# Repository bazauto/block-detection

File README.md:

# 2-Channel DCC Block Detector (Active High)

CT-based occupancy detection for the Westgate Hollow layout. Two independent
channels, each turning the current in an external current transformer into a
push-pull logic level: **HIGH (3.3 V) = block occupied, LOW (0 V) = clear**.

Single +3.3 V rail, fed in through the output header. Board is **48 × 38 mm**,
2 layers, four M2 mounting holes.

## Why build this

**So that a broken cable or connection under the layout doesn't register as a
clear block.**

The off-the-shelf detectors used so far are active low: they pull their output to
0 V when a block is occupied, and leave it open when clear. The feedback node's
inputs are pulled up, so a broken wire floats high, and that reads exactly like a
clear block, the permissive state (`bazauto/layout-feedback#9`).

This board is **active high**: occupied drives 3.3 V, clear drives 0 V. A broken
wire into a pulled-up input now floats to the *occupied* side.

## Status

**Revision 1.0: 10 boards ordered from PCBWay, awaiting delivery.** Nothing has
been measured on hardware yet.

---

## Files

| File | What it is |
|---|---|
| `bazauto-block-detection.kicad_sch` | Schematic (KiCad 10 format) |
| `bazauto-block-detection.kicad_pcb` | 2-layer PCB, fully routed |
| `bazauto-block-detection.kicad_sym` | Project symbols: `TLV9002IDGKR`, `TLV3212IDGKR` |
| `sym-lib-table` | Project symbol library table. There is no project footprint table: every footprint comes from the stock KiCad libraries and is stored in the board file |
| `bom.csv` | Bill of materials, grouped |
| `fab/rev-1.0/` | **Revision 1.0 as sent to fab**: Gerbers, drill files, Gerber job file, position file, the zipped Gerber set, and `SOURCE.txt` fingerprinting the board they came from. See [Fabrication revisions](#fabrication-revisions) |
| `BOM_PCBWay_bazauto-block-detection.xlsx` | **Not in the repo.** `bom.csv` poured into PCBWay's template, ready to upload. Generate it locally; see [Regenerating](#regenerating) |
| `scripts/` | Generators and checkers — see [Regenerating](#regenerating) |

Everything else (resistors, caps, diodes, connectors, trimmers) comes from the
stock KiCad 10 libraries, so the project opens on any standard install.

---

## Circuit

Each channel is the same chain:

```
CT ─ terminal block ─ burden ─ ESD clamp ─ 1k ─ precision peak detector ─ comparator ─ OUT
     J1 / J2          R1,R2,R3  D1 / D2   R4/R5   U1 + D3/D4 + C3/C4 + R8/R9   U2      J3
                      + JP1
```

**Burden.** The CT secondary is loaded across the input terminals.
Channel 1 is switchable, channel 2 is fixed:

| Channel | JP1 | Burden | Use |
|---|---|---|---|
| 1 | open | 1.1 kΩ | Programming track (service-mode ACK pulse) |
| 1 | fitted | 1.1 k ∥ 110 R = **100.0 Ω** | Standard track |
| 2 | — | 100 Ω fixed | Standard track only |

The parallel combination is exact: 1100 × 110 / 1210 = 100.0 Ω.

**Clamp.** D1/D2 (BAT54S, series pair) clamp the input to roughly −0.3 V /
+3.6 V. R4/R5 (1 k) then limit the current into the op-amp's input structure on
the negative half-cycle — the CT output is bipolar and a single-supply op-amp
input sits at the very edge of its absolute maximum without them.

**Peak detector.** The op-amp drives D3/D4 with the diode *inside* the feedback
loop, so the forward drop is divided out by the loop gain — no 0.6 V loss on a
signal this small. R6/R7 (100 Ω) sit between the op-amp output and the diode:
they are inside the loop too, and stop the RRIO output from ringing into the
10 µF hold capacitor. C3/C4 hold the envelope, R8/R9 bleed it away.

**Comparator.** The envelope goes to +IN, the trimmer wiper to −IN, and the
push-pull output drives the header directly. R10/R11 (10 M) add positive
feedback so the output does not chatter as the envelope crosses the threshold.

---

## Setting up

Time constants and tuning, all measurable on the board:

- **Release time.** R8/R9 × C3/C4 = 100 kΩ × 10 µF ≈ **1 s** to decay. That
  doubles as debounce for dirty wheels. For a faster release drop the bleed
  resistor — 10 k gives ≈ 100 ms.
- **Hysteresis.** V_hyst ≈ 3.3 V × R_bleed / R_hyst = 3.3 × 100 k / 10 M
  ≈ **33 mV**. Lower R10/R11 for more.
- **Threshold.** With the block clear, turn RVn until OUTn just goes low, then
  back off about 10 %.

Test points, all on the top side:

| TP | Net | Use |
|---|---|---|
| TP1 / TP3 | VREF1 / VREF2 | Trimmer wiper — the threshold you have dialled in |
| TP2 / TP4 | ENV1 / ENV2 | Peak-detector output — the rectified envelope |
| TP5 | GND | Scope ground |

---

## ⚠ Known concerns with revision 1.0

**1. The signal chain has no gain, and that makes the threshold hard to set.**

This is the one thing worth changing. The detector is a unity-gain rectifier, so
the comparator threshold has to be set in the millivolt region. With a 1:100 CT
and a 100 Ω burden, 10 mA of track current gives about 10 mV at the envelope
node. The trimmer spans the full 0–3.3 V across 10 kΩ, so 10 mV is **0.3 % of
its travel** — a fraction of one turn on a 12-turn trimmer — and it is the same
order as the comparator's own input offset voltage. Setting it repeatably will
be unpleasant, and it will drift.

The cheap fix is one resistor: put ~330 kΩ in series between +3V3 and the top of
each trimmer (RV1 pin 1, RV2 pin 1). The wiper then covers roughly 0–100 mV
instead of 0–3.3 V, giving about 30× the resolution and swamping nothing else.
The alternative is to give the op-amp stage gain instead of running it at unity.

**Revision 1.0, as ordered, does not include this change** (there is no 330 kΩ
part in `bom.csv`). Sizing it properly needs the CT's actual turns ratio. It
affects two nets and about 4 mm of track.

**2. Verify the TLV3212IDGKR pinout against the datasheet.** The comparator
symbol uses the industry-standard 8-pin dual layout — 1=OUTA, 2=INA−, 3=INA+,
4=GND, 5=INB+, 6=INB−, 7=OUTB, 8=V+ — which is what TLV3202IDGKR uses in the
same DGK package. I could not confirm TLV3212's pin assignment from a datasheet
in this session. **TLV3202IDGKR is a verified drop-in** if you would rather not
check. Same for TLV9002IDGKR, though that one follows the universal dual-op-amp
pinout and is not in doubt.

**3. AGND is the plane, not a separate net.** The spec asked for the filter
returns to go to AGND *and* for a solid, unbroken ground plane. Those pull in
opposite directions — a genuine second net needs a split, and a split is exactly
what section 6 forbids. I used one continuous GND pour and kept the analog
returns physically local instead: C3/C4 and R8/R9 ground through their own vias
straight into the plane, a few millimetres from the op-amp's own ground via.

---

## Layout

- **B.Cu is a ground pour.** F.Cu carries the signals plus a second GND pour in
  the gaps. 30 ground vias tie the two together: 16 taking SMD ground pads
  straight down to the plane, 14 stitching the pours across the board.
- **+3V3** runs as a perimeter ring (top edge, right edge, bottom edge) with a
  spine threaded through the gap between the two pad rows of U1 and U2, so it
  never crosses a channel's signal path.
- The two channels are mirrored top and bottom about the board centreline, with
  the shared dual op-amp and comparator between them. Both ICs are rotated so
  channel A faces the top band and channel B the bottom.
- 0.1 µF decoupling (C1, C2) sits against each IC's V+ pin; C5 is the 10 µF bulk.

**Where the ground plane is interrupted.** Four short bottom-layer hops let
crossing nets pass each other, 8.60 mm of track in total on a 1824 mm² board:

| Net | From → to | Length |
|---|---|---|
| +3V3 | (20.20, 22.00) → (20.20, 24.00) | 2.00 mm |
| /OUT1 | (42.20, 18.30) → (43.80, 18.30) | 1.60 mm |
| /OUT2 | (31.90, 22.60) → (33.45, 22.60) | 1.55 mm |
| OA2 out | (21.50, 22.75) → (21.50, 26.20) | 3.45 mm |

`scripts/check_plane.py` audits this and reports which analog nets pass over a
void. Current result: **the CT input rails, both op-amp inputs, ENV1 and VREF1
have completely unbroken copper beneath them.** Four crossings remain, all in
channel 2's middle band — ENV2 twice, VREF2 once, channel 2's op-amp output
once — and in each the trace crosses a void under 1 mm wide. Those nets carry a
rectified DC envelope and a DC threshold reference, where a sub-millimetre
detour in the return path at DCC frequencies is not a real effect. If you want them gone, the honest fix is a 4-layer stack-up, not
more clever 2-layer routing.

One placement change from your version: **C1 moved 0.65 mm right** (to x = 23.45)
so that channel 2's feedback trace and op-amp output each get their own corridor
past it. Everything else is where you left it.

---

## Regenerating

Run with KiCad's bundled Python, from the project directory:

```sh
K="C:/Program Files/KiCad/10.0"

python scripts/gen_schematic.py         # schematic + project symbol lib
python scripts/verify_netlist.py        # netlist vs. design intent
"$K/bin/python.exe" scripts/route_pcb.py    # routing + pours (placement is preserved)
"$K/bin/python.exe" scripts/check_board.py  # placement + board-vs-schematic nets
"$K/bin/python.exe" scripts/check_plane.py  # ground-plane audit
```

`route_pcb.py` loads the existing board, so hand-adjusted placement and
silkscreen survive; it only rebuilds tracks, vias and zones.

| Script | Does |
|---|---|
| `gen_schematic.py` | Builds the schematic from real KiCad library symbols; wires are computed from actual pin coordinates |
| `kicadlib.py` | S-expression reader/writer and symbol-library helpers |
| `probe_transform.py` | Derives KiCad's symbol placement transform empirically from its own demo files |
| `verify_netlist.py` | Compares the extracted netlist against the intended one, net by net |
| `route_pcb.py` | Routing, ground pours, silkscreen legends |
| `check_board.py` | Courtyard overlaps, off-board parts, board nets vs. schematic |
| `check_plane.py` | Bottom-layer voids and which analog nets cross them |
| `make_pcbway_bom.py` | Fills PCBWay's BOM template; fails if it has drifted from `bom.csv`. Needs PCBWay's sample BOM template saved locally as `Sample_BOM_PCBWay.xlsx`. It's PCBWay's file, so it isn't committed, and neither is the output. |
| `check_fab_outputs.py` | Checks the newest `fab/rev-X.Y/` against the board it was generated from; `--record` writes that revision's `SOURCE.txt`. Plain Python, needs `kicad-cli` on PATH or `KICAD_CLI` set |

---

## Fabrication revisions

Each set of files sent to a board house lives in its own `fab/rev-X.Y/` folder
and is never regenerated in place, so the repo always holds exactly what a
revision was. Each revision is also tagged in git (`rev-1.0`).

`fab/rev-X.Y/SOURCE.txt` records the SHA-256 of the board file (line endings
normalised) that its outputs came from. CI runs `scripts/check_fab_outputs.py`:

- **Board unchanged since the newest revision:** it regenerates the outputs and
  fails if the committed ones differ. That catches Gerbers left stale after a
  board edit, and a zip that disagrees with the loose files. Gerbers are compared
  by the geometry they draw, because KiCad doesn't write primitives in a stable
  order.
- **Board changed:** work on the next revision is under way. It reports a notice
  and passes.

To cut a new revision, for example 1.1:

1. Plot Gerbers, drill files (Excellon, PTH and NPTH separate) and the position
   file (CSV, mm, both sides) into `fab/rev-1.1/`, and zip the Gerbers, the
   Gerber job file and the drill files as `bazauto-block-detection.zip` there.
2. `python scripts/check_fab_outputs.py --record rev-1.1`
3. `python scripts/check_fab_outputs.py`, which must report all outputs matching.
4. Land it through a PR, then tag the merge commit `rev-1.1`.

---

## Verification

Everything below was run against the files in this directory:

```
kicad-cli sch erc            0 errors, 0 warnings
verify_netlist.py            all 17 nets match design intent, no unconnected pins
kicad-cli pcb drc            0 violations, 0 unconnected items
check_board.py               37 footprints, 0 problems (no overlaps, nets match schematic)
check_plane.py               8.60 mm bottom-layer track; 4 analog crossings (see above)
```

CI re-runs the two `kicad-cli` checks and `check_fab_outputs.py` on every pull
request (see `.github/workflows/ci.yml`). DRC there runs with `--schematic-parity` at error
severity. At warning severity the parity check reports 80 cosmetic mismatches:
footprints saved without their library prefix, and field text such as a
Datasheet of `''` against `~`. None is a net or connection mismatch.

Gerbers and drill files for revision 1.0 are in `fab/rev-1.0/`, and regenerating
them from the current board reproduces them exactly. Nothing has been measured on
hardware yet. The threshold-resolution concern above is analysis, not a bench
result.

---

## Licence

Copyright © 2026 Paul Barrett.

| Material | Licence |
|---|---|
| **The hardware design**: schematic, board, project symbol library, BOM, Gerbers and drill files, and the enclosure model (`enclosure/`, except `check_fit.py`) | [CERN-OHL-P-2.0](LICENSE) |
| **Software**: everything in `scripts/`, and `enclosure/check_fit.py` | [MIT](LICENSE-MIT) |

Source location: <https://github.com/bazauto/block-detection>

Third-party material, notably the KiCad library symbols the project symbols are
derived from, is listed in [THIRD-PARTY-NOTICES.md](THIRD-PARTY-NOTICES.md).

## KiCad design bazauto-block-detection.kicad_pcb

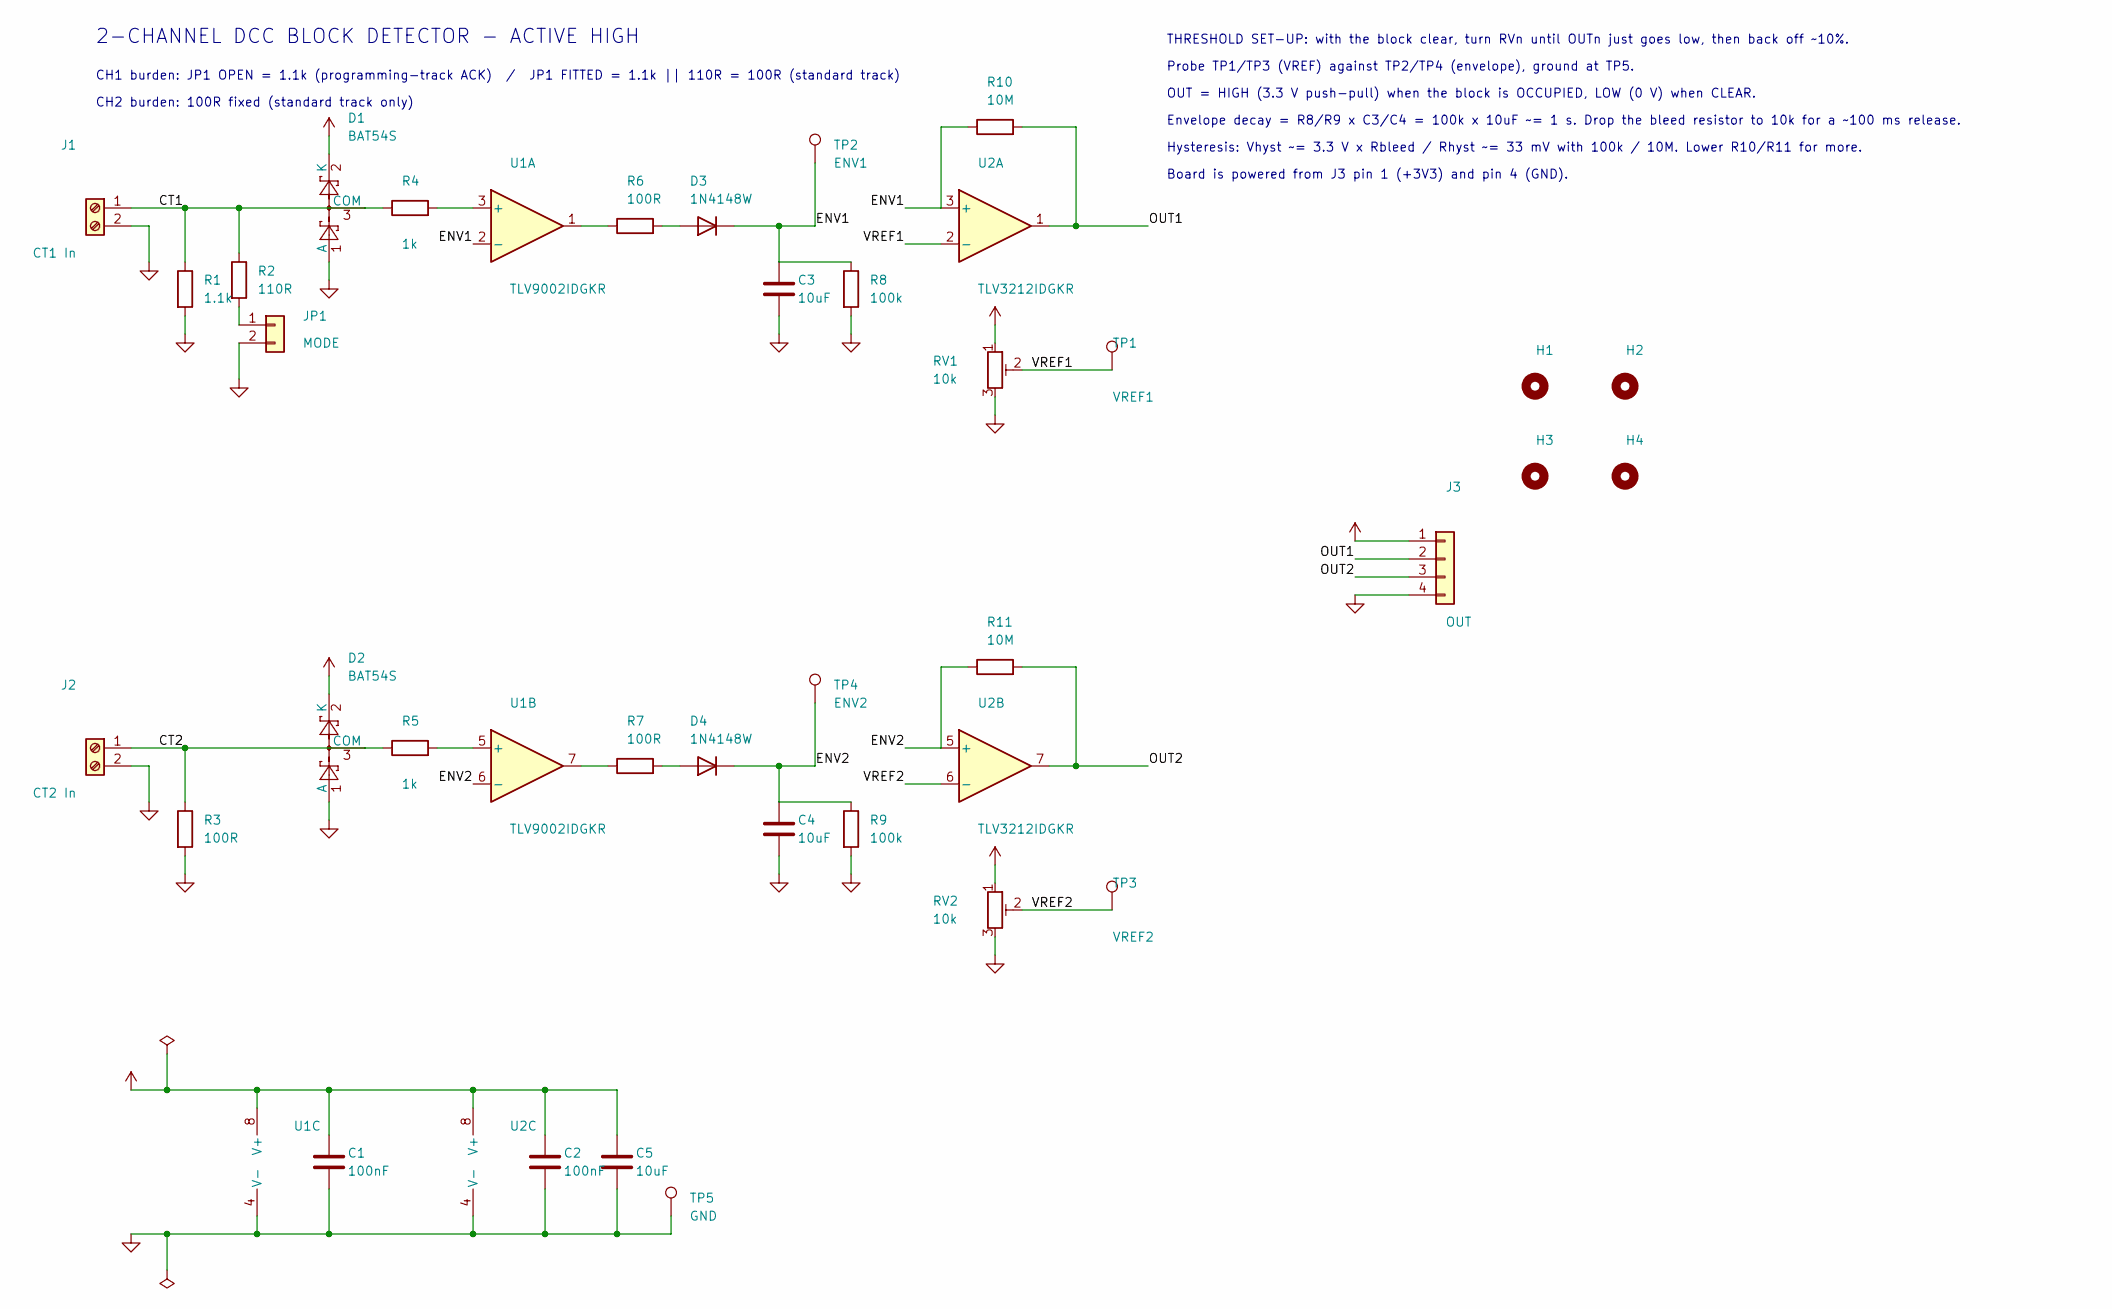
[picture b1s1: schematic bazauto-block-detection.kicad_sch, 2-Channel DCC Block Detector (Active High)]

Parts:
C1, C2: 100nF; C_0805_2012Metric; Voltage 25V
C3, C4, C5: 10uF; C_0805_2012Metric; Voltage 25V
D1, D2: BAT54S; SOT-23
D3, D4: 1N4148W; D_SOD-123
H1, H2, H3, H4: MountingHole; MountingHole_2.2mm_M2
J1: CT1 In; TerminalBlock_Phoenix_PT-1,5-2-3.5-H_1x02_P3.50mm_Horizontal
J2: CT2 In; TerminalBlock_Phoenix_PT-1,5-2-3.5-H_1x02_P3.50mm_Horizontal
J3: OUT; PinHeader_1x04_P2.54mm_Vertical
JP1: MODE; PinHeader_1x02_P2.54mm_Vertical
R1: 1.1k; R_1206_3216Metric; Tolerance 1%
R2: 110R; R_1206_3216Metric; Tolerance 1%
R3: 100R; R_1206_3216Metric; Tolerance 1%
R4, R5: 1k; R_0805_2012Metric
R6, R7: 100R; R_0805_2012Metric
R8, R9: 100k; R_0805_2012Metric
R10, R11: 10M; R_0805_2012Metric
RV1, RV2: 10k; Potentiometer_Bourns_3269W_Vertical
TP1: VREF1; TestPoint_Pad_D1.5mm
TP2: ENV1; TestPoint_Pad_D1.5mm
TP3: VREF2; TestPoint_Pad_D1.5mm
TP4: ENV2; TestPoint_Pad_D1.5mm
TP5: GND; TestPoint_Pad_D1.5mm
U1: TLV9002IDGKR; MSOP-8_3x3mm_P0.65mm
U2: TLV3212IDGKR; MSOP-8_3x3mm_P0.65mm

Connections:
+3V3: C1.1, C2.1, C5.1, D1.2 (K), D2.2 (K), J3.1, RV1.1, RV2.1, U1.8 (V+), U2.8 (V+)
/CT1: D1.3 (COM), J1.1, R1.1, R2.1, R4.1
/CT2: D2.3 (COM), J2.1, R3.1, R5.1
/ENV1: C3.1, D3.1 (K), R8.1, R10.1, TP2.1, U1.2 (-), U2.3 (+)
/ENV2: C4.1, D4.1 (K), R9.1, R11.1, TP4.1, U1.6 (-), U2.5 (+)
/OUT1: J3.2, R10.2, U2.1
/OUT2: J3.3, R11.2, U2.7
/VREF1: RV1.2, TP1.1, U2.2 (-)
/VREF2: RV2.2, TP3.1, U2.6 (-)
GND: C1.2, C2.2, C3.2, C4.2, C5.2, D1.1 (A), D2.1 (A), J1.2, J2.2, J3.4, JP1.2, R1.2, R3.2, R8.2, R9.2, RV1.3, RV2.3, TP5.1, U1.4 (V-), U2.4 (V-)
unnamed: D3.2 (A), R6.2
unnamed: D4.2 (A), R7.2
unnamed: JP1.1, R2.2
unnamed: R6.1, U1.1
unnamed: R7.1, U1.7
unnamed: R4.2, U1.3 (+)
unnamed: R5.2, U1.5 (+)

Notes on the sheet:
2-CHANNEL DCC BLOCK DETECTOR - ACTIVE HIGH
CH1 burden: JP1 OPEN = 1.1k (programming-track ACK) / JP1 FITTED = 1.1k || 110R = 100R (standard track)
CH2 burden: 100R fixed (standard track only)
THRESHOLD SET-UP: with the block clear, turn RVn until OUTn just goes low, then back off ~10%.
Probe TP1/TP3 (VREF) against TP2/TP4 (envelope), ground at TP5.
OUT = HIGH (3.3 V push-pull) when the block is OCCUPIED, LOW (0 V) when CLEAR.
Envelope decay = R8/R9 x C3/C4 = 100k x 10uF ~= 1 s. Drop the bleed resistor to 10k for a ~100 ms release.
Hysteresis: Vhyst ~= 3.3 V x Rbleed / Rhyst ~= 33 mV with 100k / 10M. Lower R10/R11 for more.
Board is powered from J3 pin 1 (+3V3) and pin 4 (GND).

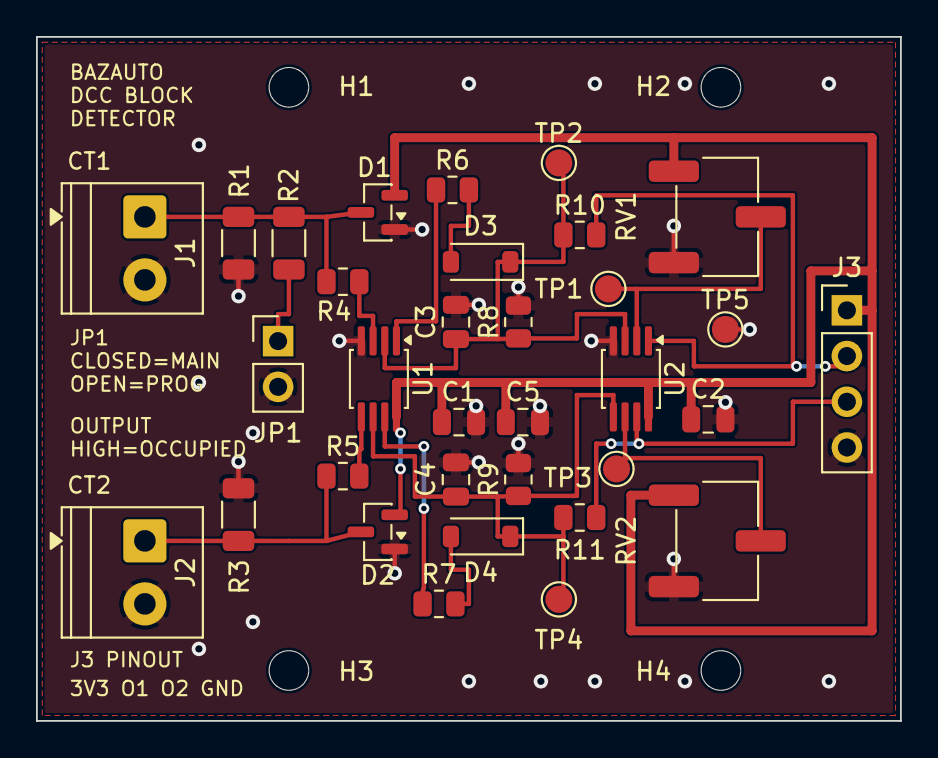
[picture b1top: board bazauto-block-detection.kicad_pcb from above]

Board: 2 copper layers, 48.0 x 38.0 mm, 37 parts (0 on the bottom side), 17 nets.

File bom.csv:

Refs,Value,Footprint,Tolerance,Rating,Description,Alternative Part Number
"C1,C2",100nF,Capacitor_SMD:C_0805_2012Metric,,25V,,
C3-C5,10uF,Capacitor_SMD:C_0805_2012Metric,,25V,,
"D1,D2",BAT54S,Package_TO_SOT_SMD:SOT-23,,,,
"D3,D4",1N4148W,Diode_SMD:D_SOD-123,,,,
J1,CT1 In,"TerminalBlock_Phoenix:TerminalBlock_Phoenix_PT-1,5-2-3.5-H_1x02_P3.50mm_Horizontal",,,,
J2,CT2 In,"TerminalBlock_Phoenix:TerminalBlock_Phoenix_PT-1,5-2-3.5-H_1x02_P3.50mm_Horizontal",,,,
J3,OUT,Connector_PinHeader_2.54mm:PinHeader_1x04_P2.54mm_Vertical,,,,
JP1,MODE,Connector_PinHeader_2.54mm:PinHeader_1x02_P2.54mm_Vertical,,,,
R1,1.1k,Resistor_SMD:R_1206_3216Metric,1%,,,
R2,110R,Resistor_SMD:R_1206_3216Metric,1%,,,
R3,100R,Resistor_SMD:R_1206_3216Metric,1%,,,
"R4,R5",1k,Resistor_SMD:R_0805_2012Metric,,,,
"R6,R7",100R,Resistor_SMD:R_0805_2012Metric,,,,
"R8,R9",100k,Resistor_SMD:R_0805_2012Metric,,,,
"R10,R11",10M,Resistor_SMD:R_0805_2012Metric,,,,
"RV1,RV2",10k,Potentiometer_SMD:Potentiometer_Bourns_3269W_Vertical,,,,
U1,TLV9002IDGKR,Package_SO:MSOP-8_3x3mm_P0.65mm,,,,
U2,TLV3212IDGKR,Package_SO:MSOP-8_3x3mm_P0.65mm,,,,TLV7012DGKR
